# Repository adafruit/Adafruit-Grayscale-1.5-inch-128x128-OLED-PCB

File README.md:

## Adafruit Grayscale 1.5" 128x128 OLED Graphic Display - STEMMA QT / Qwiic PCB

<a href="http://www.adafruit.com/products/4741"><br/>
Click here to purchase one from the Adafruit shop</a>

PCB files for the Adafruit Grayscale 1.5" 128x128 OLED Graphic Display - STEMMA QT / Qwiic. 

Format is EagleCAD schematic and board layout
* https://www.adafruit.com/product/4741

### Description

This OLED goes out to all the fans who want more pixels! Normally our 128x64 OLEDs are the biggest ones we've stocked that can use I2C. This one is a whopping 128x128 pixels and it even has an extra bonus - it can do grayscale pixels! Yep, you get the same crispness of a monochome OLED but with 16 levels of grayscale.

This display is a petite 1.5" diagonal , but very readable due to the high contrast of an OLED display. This display is made of 128x128 individual grayscale OLED pixels, each one is turned on or off by the controller chip. Because the display makes its own light, no backlight is required. This reduces the power required to run the OLED and is why the display has such high contrast; we really like these miniature displays for their crispness!

The driver chip, SSD1327 can communicate in two ways: I2C or SPI. The OLED itself require a 3.3V and 12V power supply and 3.3V logic levels for communication. We include a 3.3V regulator and 12V boost converter, and all pins are fully level shifted so you can use with 3V or 5V devices!

If you are using I2C, we've included [SparkFun qwiic](https://www.sparkfun.com/qwiic) compatible [STEMMA QT](https://learn.adafruit.com/introducing-adafruit-stemma-qt) connectors for the I2C bus **so you don't even need to solder!** Plug and play with any board that has a Qwiic or STEMMA QT connector for effortless prototyping and development.

This display, being 16-level (4-bit) grayscale and 128x128 requires 128 * 128 * 4 bits = 8KB of SRAM to buffer. So **you can't use it with a small chip such as the Arduino UNO** (ATmega328 or 32u4). Pick a microcontroller or microcomputer with 16KB+ RAM - a SAMD21, SAMD51, ESP, nRF52, Teensy, etc will do an excellent job. As long as you have I2C or SPI interface available, you're good to go - SPI will be much faster but I2C requires fewer pins.

[We have both Arduino](https://github.com/adafruit/Adafruit_SSD1327) and [CircuitPython support](https://github.com/adafruit/Adafruit_CircuitPython_SSD1327) for this display.

Please note that OLED displays are made of hundreds of...OLEDs! That means each pixel is a little organic LED, and if its kept on for over 1000 hours it'll start to dim. If you want to keep the display uniformly bright, please turn off the display (set the pixels off) when it isn't needed to keep them from dimming.

### License

Adafruit invests time and resources providing this open source design, please support Adafruit and open-source hardware by purchasing products from [Adafruit](https://www.adafruit.com)!

Designed by Limor Fried/Ladyada for Adafruit Industries.

Creative Commons Attribution/Share-Alike, all text above must be included in any redistribution. 
See license.txt for additional details.

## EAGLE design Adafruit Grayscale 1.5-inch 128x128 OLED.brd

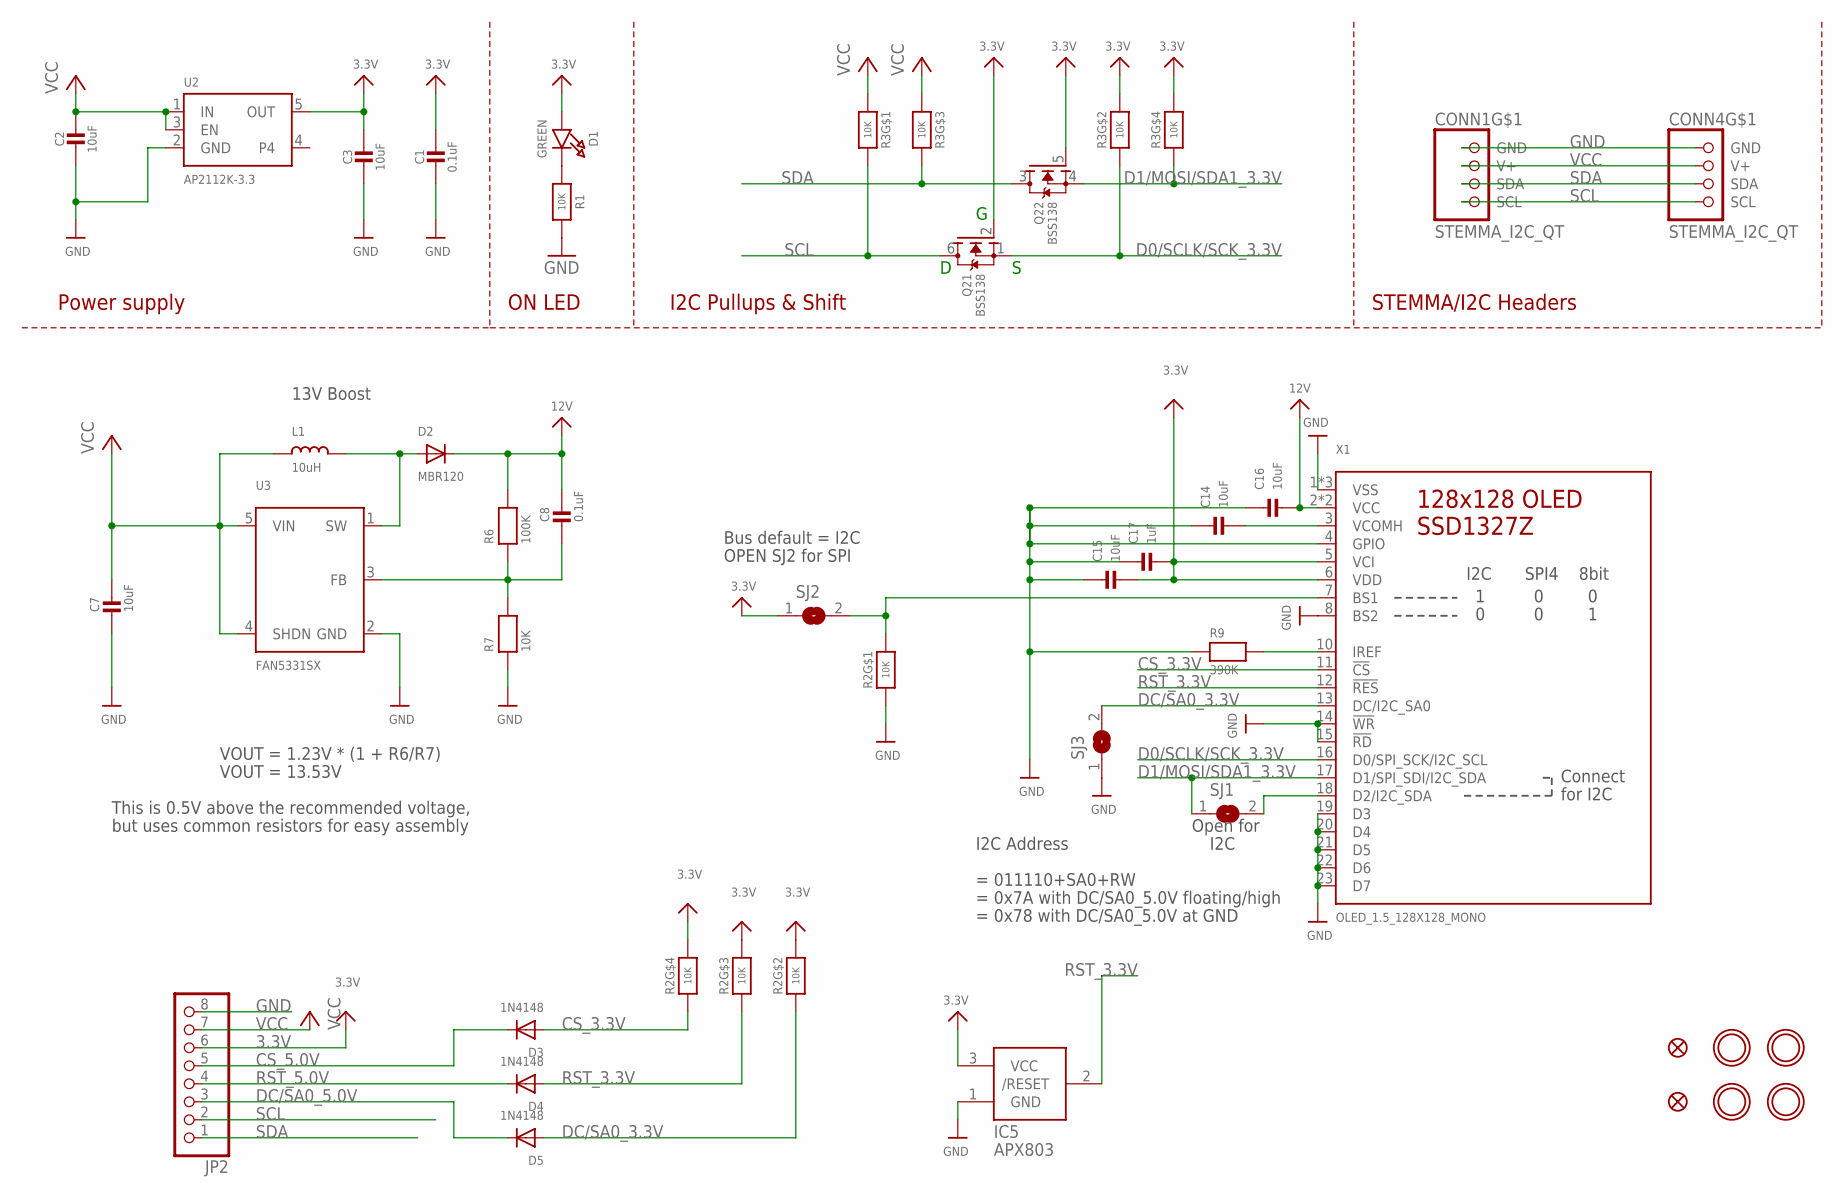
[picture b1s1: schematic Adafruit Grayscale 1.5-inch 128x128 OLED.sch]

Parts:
C1, C8: 0.1uF; 0603-NO
C2, C3, C7, C14, C15, C16: 10uF; 0805-NO
C17: 1uF; 0603-NO
CONN1, CONN4: STEMMA_I2C_QT; JST_SH4
D1: GREEN; CHIPLED_0603_NOOUTLINE
D2: MBR120; SOD-123
D3, D4, D5: 1N4148; SOD-323
FID3, FID4: FIDUCIAL_1MM
IC5: APX803; SOT23
JP2: HEADER-1X870MIL; 1X08_ROUND_70
L1: 10uH; INDUCTOR_1007
Q2: BSS138; SOT363
R1, R7: 10K; 0603-NO
R2, R3: 10K; RESPACK_4X0603
R6: 100K; 0603-NO
R9: 390K; 0603-NO
SJ1, SJ2: SOLDERJUMPERCLOSED; SOLDERJUMPER_CLOSEDWIRE
SJ3: SOLDERJUMPER; SOLDERJUMPER_ARROW_NOPASTE
U2: AP2112K-3.3; SOT23-5
U3: FAN5331SX; SOT23-5@1
U$1, U$17, U$19, U$21: MOUNTINGHOLE2.5; MOUNTINGHOLE_2.5_PLATED
X1: OLED_1.5_128X128_MONO; OLED_1.5IN_128X128MONO

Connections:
3.3V: C1.1, C3.1, C15.2, C17.2, D1.A, IC5.3 (VCC), JP2.6, Q2.2 (G), Q2.5 (G), R2.5 (2), R2.6 (2), R2.7 (2), R3.2 (1), R3.4 (1), SJ2.1, U2.5 (OUT), X1.5 (VCI), X1.6 (VDD)
12V: C8.1, C16.2, D2.C, R6.2, X1.2 (VCC), X1.24 (VCC)
CS_3.3V: D3.A, R2.4 (1), X1.11 (!CS)
CS_5.0V: D3.C, JP2.5
D0/SCLK/SCK_3.3V: Q2.1 (S), R3.7 (2), X1.16 (D0/SPI_SCK/I2C_SCL)
D1/MOSI/SDA1_3.3V: Q2.4 (S), R3.5 (2), SJ1.1, X1.17 (D1/SPI_SDI/I2C_SDA)
DC/SA0_3.3V: D5.A, R2.2 (1), SJ3.2, X1.13 (DC/I2C_SA0)
DC/SA0_5.0V: D5.C, JP2.3
GND: C1.2, C2.2, C3.2, C7.2, C14.1, C15.1, C16.1, C17.1, CONN1.1 (GND), CONN4.1 (GND), IC5.1 (GND), JP2.8, R1.2, R2.1, R7.1, R9.1, SJ3.1, U2.2 (GND), U3.2 (GND), X1.1 (VSS), X1.4 (GPIO), X1.8 (BS2), X1.9 (VSS), X1.14 (!WR), X1.15 (!RD), X1.19 (D3), X1.20 (D4), X1.21 (D5), X1.22 (D6), X1.23 (D7), X1.25 (VSS)
unnamed: D1.C, R1.1
unnamed: D2.A, L1.P$2 (2), U3.1 (SW)
unnamed: C8.2, R6.1, R7.2, U3.3 (FB)
unnamed: R2.8 (2), SJ2.2, X1.7 (BS1)
unnamed: R9.2, X1.10 (IREF)
unnamed: C14.2, X1.3 (VCOMH)
unnamed: SJ1.2, X1.18 (D2/I2C_SDA)
RST_3.3V: D4.A, IC5.2 (/RESET), R2.3 (1), X1.12 (!RES)
RST_5.0V: D4.C, JP2.4
SCL: CONN1.4 (SCL), CONN4.4 (SCL), JP2.2, Q2.6 (D), R3.8 (2)
SDA: CONN1.3 (SDA), CONN4.3 (SDA), JP2.1, Q2.3 (D), R3.6 (2)
VCC: C2.1, C7.1, CONN1.2 (V+), CONN4.2 (V+), JP2.7, L1.P$1 (1), R3.1, R3.3 (1), U2.1 (IN), U2.3 (EN), U3.4 (SHDN), U3.5 (VIN)

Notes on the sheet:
I2C Pullups & Shift
STEMMA/I2C Headers
ON LED
Power supply
Bus default = I2C
OPEN SJ2 for SPI
= 011110+SA0+RW
= 0x7A with DC/SA0_5.0V floating/high
= 0x78 with DC/SA0_5.0V at GND
I2C Address
Open for
I2C
VOUT = 1.23V * (1 + R6/R7)
VOUT = 13.53V
This is 0.5V above the recommended voltage,
but uses common resistors for easy assembly
13V Boost

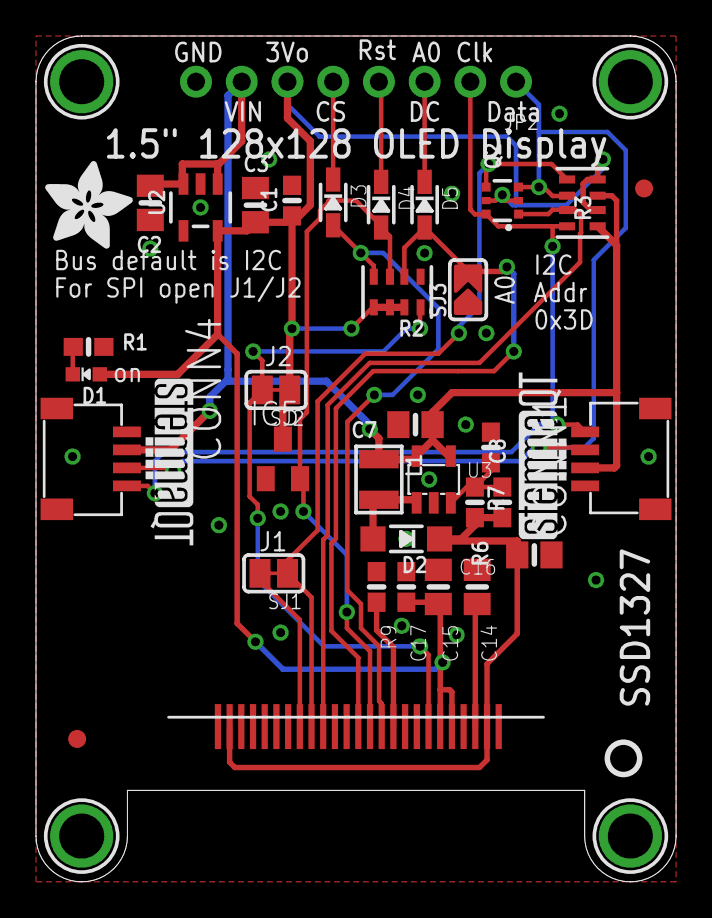
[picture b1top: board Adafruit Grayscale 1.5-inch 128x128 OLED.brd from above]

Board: 2 copper layers, 35.6 x 47.0 mm, 42 parts (1 on the bottom side), 21 nets.

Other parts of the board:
U$8: ADAFRUIT_5MM
U$20, U$31: STEMMAQT
U$25: PCBFEAT-REV-040

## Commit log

2020-11-05 Added initial files

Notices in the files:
parts and their libraries:
microbuilder: This work is placed in the public domain, and may be freely used for commercial and non-commercial work with the following conditions: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
